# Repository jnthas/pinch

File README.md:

# Pinch: a password storage for nerds

## Featuring video

## What is Pinch?

Pinch is an open-source, personal and portable device capable of storing, retrieving and entering your passwords on demand. It is a physical device with no internet access and only works through manual activation.
Pinch is the size of a USB flash drive. It has a USB interface, two buttons and a three digit display which are used to select and confirm the desired password. When confirming, simply put the focus on the password field and the Pinch will enter it for you.

## How does Pinch work?

Pinch has three modes of operation
- The first state is when your device is locked. To start using it, you need to enter a three-digit PIN, this will prevent others who have easy access to your device.
- The second is the default one, the Owner Mode where Pinch acts like a keyboard. When you plug it into the computer, it can enter passwords as if it were you without anyone seeing it.
- The third one, is the Admin Mode. In this mode you can register new passwords, set parameters and list existing labels via serial communication using a CLI. For security reasons, you cannot retrieve passwords in this mode, only register them. Select the desired slot on the device and enter the label and password on the command line. Disconnect and connect again and the password is now available.

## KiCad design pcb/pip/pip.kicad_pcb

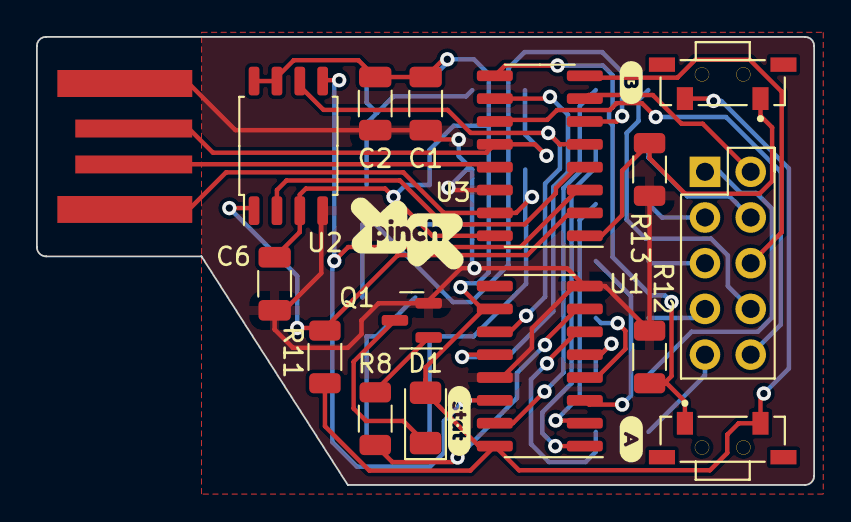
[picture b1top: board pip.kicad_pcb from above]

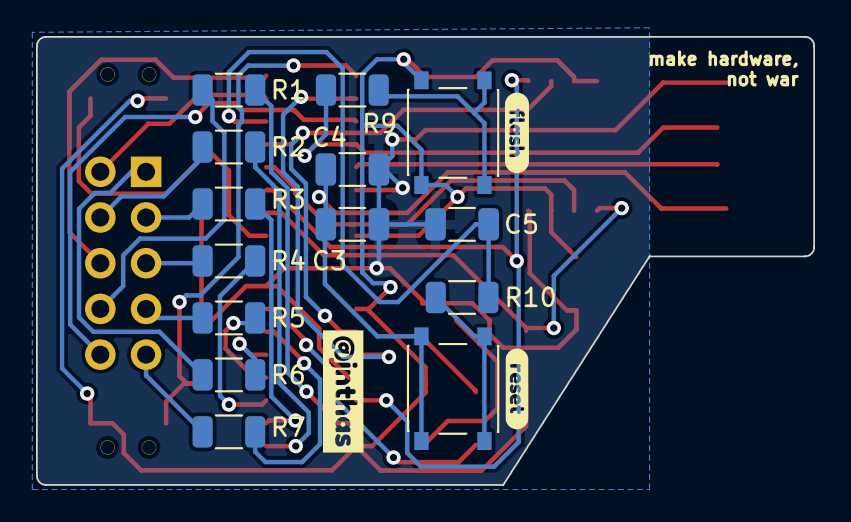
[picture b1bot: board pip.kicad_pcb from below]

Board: 2 copper layers, 43.2 x 24.9 mm, 36 parts (17 on the bottom side), 35 nets.

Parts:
C1, C2, C3, C5, C6: 0.1uF; C_1206_3216Metric
C4: 4.7uF; C_1206_3216Metric
D1: LED; LED_1206_3216Metric
DS1: NET-2531AB-11; Display_2531AB
J1: USBPCB; USB-A-PCB
Q1: BC847; SOT-23
R1, R2, R3, R4, R5, R6, R7, R8: 1K; R_1206_3216Metric
R9, R12, R13: 10K; R_1206_3216Metric
R10: 330R; R_1206_3216Metric
R11: 4.7K; R_1206_3216Metric
SW1: FLASH; SW_Push_45x45mm_H1.5mm
SW2: RESET; SW_Push_45x45mm_H1.5mm
SW3: BUTTON_A; SW_TL3330AF130QG
SW4: BUTTON_B; SW_TL3330AF130QG
U1: 74HC595; SOP-16_3.9x9.9mm_P1.27mm
U2: W25Q32JVSS; SOIC-8_5.23x5.23mm_P1.27mm
U3: CH552G; SOP-16_3.9x9.9mm_P1.27mm
kibuzzard-63727E71: G***; kibuzzard-63727E71
kibuzzard-63727E80: G***; kibuzzard-63727E80
kibuzzard-63728AEE: G***; kibuzzard-63728AEE
kibuzzard-63728AF8: G***; kibuzzard-63728AF8
kibuzzard-63728B2A: G***; kibuzzard-63728B2A
kibuzzard-63728C1B: G***; kibuzzard-63728C1B

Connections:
GND: C1.2, C2.2, C3.2, C4.2, C5.2, C6.1, J1.GND, Q1.2 (E), R12.1, R13.1, U1.8 (GND), U1.13 (~OE), U2.4 (GND), U3.14 (GND)
unnamed: D1.1 (K), Q1.3 (C)
unnamed: DS1.1 (f), R6.2
unnamed: DS1.2 (c), R3.2
unnamed: DS1.3 (d), R4.2
unnamed: DS1.4 (e), R5.2
unnamed: DS1.5 (g), R7.2
unnamed: DS1.7 (a), R1.2
unnamed: DS1.9 (b), R2.2
unnamed: Q1.1 (B), R8.2
unnamed: R1.1, U1.15 (QA)
unnamed: R2.1, U1.1 (QB)
unnamed: R3.1, U1.2 (QC)
unnamed: R4.1, U1.3 (QD)
unnamed: R5.1, U1.4 (QE)
unnamed: R6.1, U1.5 (QF)
unnamed: R7.1, U1.6 (QG)
unnamed: R8.1, U1.7 (QH)
unnamed: R9.2, SW1.1 (A), SW1.2 (A)
unnamed: R10.2, SW2.1 (A), SW2.2 (A)
P1.1: R12.2, SW3.1 (A), U3.9 (P1.1)
P1.4: R11.2, U2.1 (~CS), U3.2 (P1.4)
P1.5: U1.14 (SER), U2.5 (DI(IO0)), U3.3 (P1.5/MOSI)
P1.6: U2.2 (DO(IO1)), U3.4 (P1.6/MISO)
P1.7: U1.11 (SRCLK), U2.6 (CLK), U3.5 (P1.7/SCK)
P3.0: DS1.8 (CA_D2), U3.8 (P3.0/RXD)
P3.1: DS1.10 (CA_D1), U3.7 (P3.1/TXD)
P3.2: R13.2, SW4.1 (A), U3.1 (P3.2)
P3.3: U1.12 (RCLK), U3.10 (P3.3)
P3.4: DS1.6 (CA_D3), U3.11 (P3.4)
P3.6: J1.USB_DP (D+), R9.1, U3.12 (UD+/P3.6)
P3.7: J1.USB_DC (D-), U3.13 (UD-/P3.7)
RESET: C5.1, R10.1, U3.6 (RST)
VBUS: C3.1, C4.1, J1.5V (VBUS), SW2.3 (B), SW2.4 (B), U3.15 (VCC)
VCC: C1.1, C2.1, C6.2, D1.2 (A), R11.1, SW1.3 (B), SW1.4 (B), SW3.3 (B), SW4.3 (B), U1.10 (~SRCLR), U1.16 (VCC), U2.3 (IO2), U2.7 (IO3), U2.8 (VCC), U3.16 (3V3)

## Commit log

2022-09-24 initial version - PIP
2022-09-25 port flash lib
2022-10-03 implement protocol
2022-10-04 fix CDC communication error
2022-10-16 display and buttons integration
2022-10-17 refactoring components
2022-10-18 pinch core app
2022-10-22 displays current slot
2022-10-22 remove binaries
2022-10-23 misc refactoring
2022-10-23 refactoring buttons and get mem address
2022-11-02 pcb layout
2022-11-15 pcb design
2022-11-19 small fixes
2022-11-19 add pinch logo
2022-12-21 fix pinch tests
2022-12-24 locker feature
2022-12-26 create multi device
2022-12-28 multi usb device 1
2022-12-29 multi device part 2
2022-12-29 multi device part 3
2022-12-29 refactoring multi device
2022-12-30 multi device working
2023-03-16 Add resources
2023-03-16 rename file
2023-04-21 gh pages
2023-04-21 add index
2023-04-24 add css
2023-04-24 update style
2023-06-11 Create CNAME
2023-11-05 Create LICENSE
